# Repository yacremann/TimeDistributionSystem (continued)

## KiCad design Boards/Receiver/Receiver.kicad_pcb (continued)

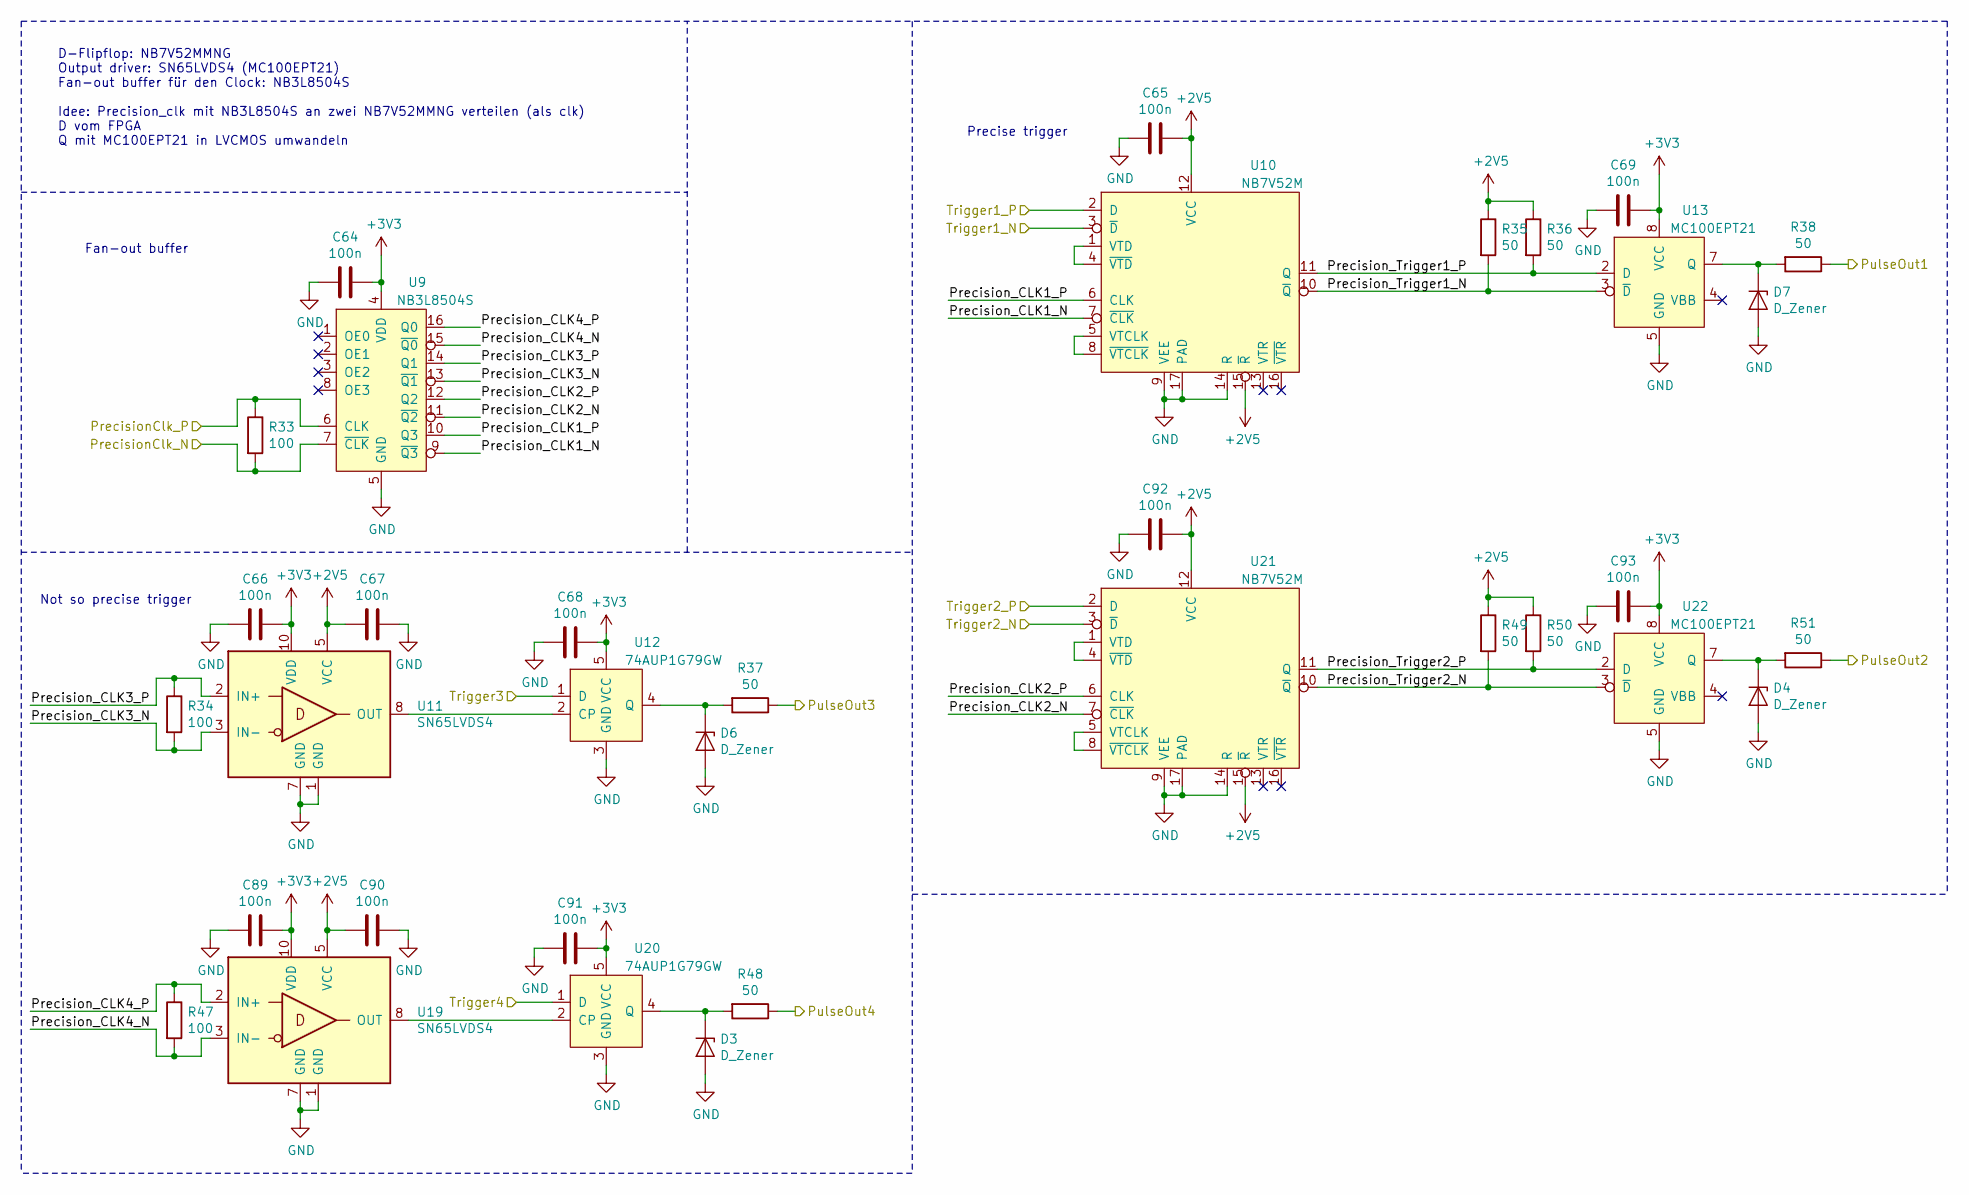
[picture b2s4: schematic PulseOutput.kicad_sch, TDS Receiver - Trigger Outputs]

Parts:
C64, C65, C66, C67, C68, C69, C89, C90, C91, C92, C93: 100n; C_0603_1608Metric
D3, D4, D6, D7: D_Zener; D_0805_2012Metric
R33, R34, R47: 100; R_0603_1608Metric
R35, R36, R37, R38, R48, R49, R50, R51: 50; R_0603_1608Metric
U9: NB3L8504S; TSSOP-16_4.4x5mm_P0.65mm
U10, U21: NB7V52M; QFN-16-1EP_3x3mm_P0.5mm_EP1.9x1.9mm
U11, U19: SN65LVDS4; Texas_R-PUQFN-N10
U12, U20: 74AUP1G79GW; SOT-353_SC-70-5_Handsoldering
U13, U22: MC100EPT21; TSSOP-8_3x3mm_P0.65mm

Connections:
+2V5: C65.1, C67.2, C90.2, C92.1, R35.1, R36.1, R49.1, R50.1, U10.12 (VCC), U10.15 (~R), U11.5 (VCC), U19.5 (VCC), U21.12 (VCC), U21.15 (~R); also elsewhere on the board
+3V3: C64.1, C66.1, C68.1, C69.1, C89.1, C91.1, C93.1, U9.4 (VDD), U11.10 (VDD), U12.5 (VCC), U13.8 (VCC), U19.10 (VDD), U20.5 (VCC), U22.8 (VCC); also elsewhere on the board
/PrecisionClk_N: R33.2, U9.7 (~CLK); also elsewhere on the board
/PrecisionClk_P: R33.1, U9.6 (CLK); also elsewhere on the board
/PulseOutput/Precision_CLK1_N: U9.9 (~Q3), U10.7 (~CLK)
/PulseOutput/Precision_CLK1_P: U9.10 (Q3), U10.6 (CLK)
/PulseOutput/Precision_CLK2_N: U9.11 (~Q2), U21.7 (~CLK)
/PulseOutput/Precision_CLK2_P: U9.12 (Q2), U21.6 (CLK)
/PulseOutput/Precision_CLK3_N: R34.2, U9.13 (~Q1), U11.3 (IN-)
/PulseOutput/Precision_CLK3_P: R34.1, U9.14 (Q1), U11.2 (IN+)
/PulseOutput/Precision_CLK4_N: R47.2, U9.15 (~Q0), U19.3 (IN-)
/PulseOutput/Precision_CLK4_P: R47.1, U9.16 (Q0), U19.2 (IN+)
/PulseOutput/Precision_Trigger1_N: R35.2, U10.10 (~Q), U13.3 (~D)
/PulseOutput/Precision_Trigger1_P: R36.2, U10.11 (Q), U13.2 (D)
/PulseOutput/Precision_Trigger2_N: R49.2, U21.10 (~Q), U22.3 (~D)
/PulseOutput/Precision_Trigger2_P: R50.2, U21.11 (Q), U22.2 (D)
/PulseOutput/PulseOut1: R38.1; also elsewhere on the board
/PulseOutput/PulseOut2: R51.1; also elsewhere on the board
/PulseOutput/PulseOut3: R37.1; also elsewhere on the board
/PulseOutput/PulseOut4: R48.1; also elsewhere on the board
/Trigger1_N: U10.3 (~D); also elsewhere on the board
/Trigger1_P: U10.2 (D); also elsewhere on the board
/Trigger2_N: U21.3 (~D); also elsewhere on the board
/Trigger2_P: U21.2 (D); also elsewhere on the board
/Trigger3: U12.1 (D); also elsewhere on the board
/Trigger4: U20.1 (D); also elsewhere on the board
GND: C64.2, C65.2, C66.2, C67.1, C68.2, C69.2, C89.2, C90.1, C91.2, C92.2, C93.2, D3.2 (A), D4.2 (A), D6.2 (A), D7.2 (A), U9.5 (GND), U10.9 (VEE), U10.14 (R), U10.17 (PAD), U11.1 (GND), U11.7 (GND), U12.3 (GND), U13.5 (GND), U19.1 (GND), U19.7 (GND), U20.3 (GND), U21.9 (VEE), U21.14 (R), U21.17 (PAD), U22.5 (GND); also elsewhere on the board
unnamed: D3.1 (K), R48.2, U20.4 (Q)
unnamed: D4.1 (K), R51.2, U22.7 (Q)
unnamed: D6.1 (K), R37.2, U12.4 (Q)
unnamed: D7.1 (K), R38.2, U13.7 (Q)
unnamed: U10.1 (VTD), U10.4 (~VTD)
unnamed: U10.5 (VTCLK), U10.8 (~VTCLK)
unnamed: U11.8 (OUT), U12.2 (CP)
unnamed: U19.8 (OUT), U20.2 (CP)
unnamed: U21.1 (VTD), U21.4 (~VTD)
unnamed: U21.5 (VTCLK), U21.8 (~VTCLK)

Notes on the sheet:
D-Flipflop: NB7V52MMNG Output driver: SN65LVDS4 (MC100EPT21) Fan-out buffer für den Clock: NB3L8504S Idee: Precision_clk mit NB3L8504S an zwei NB7V52MMNG verteilen (als clk) D vom FPGA Q mit MC100EPT21 in LVCMOS umwandeln
Precise trigger
Not so precise trigger
Fan-out buffer

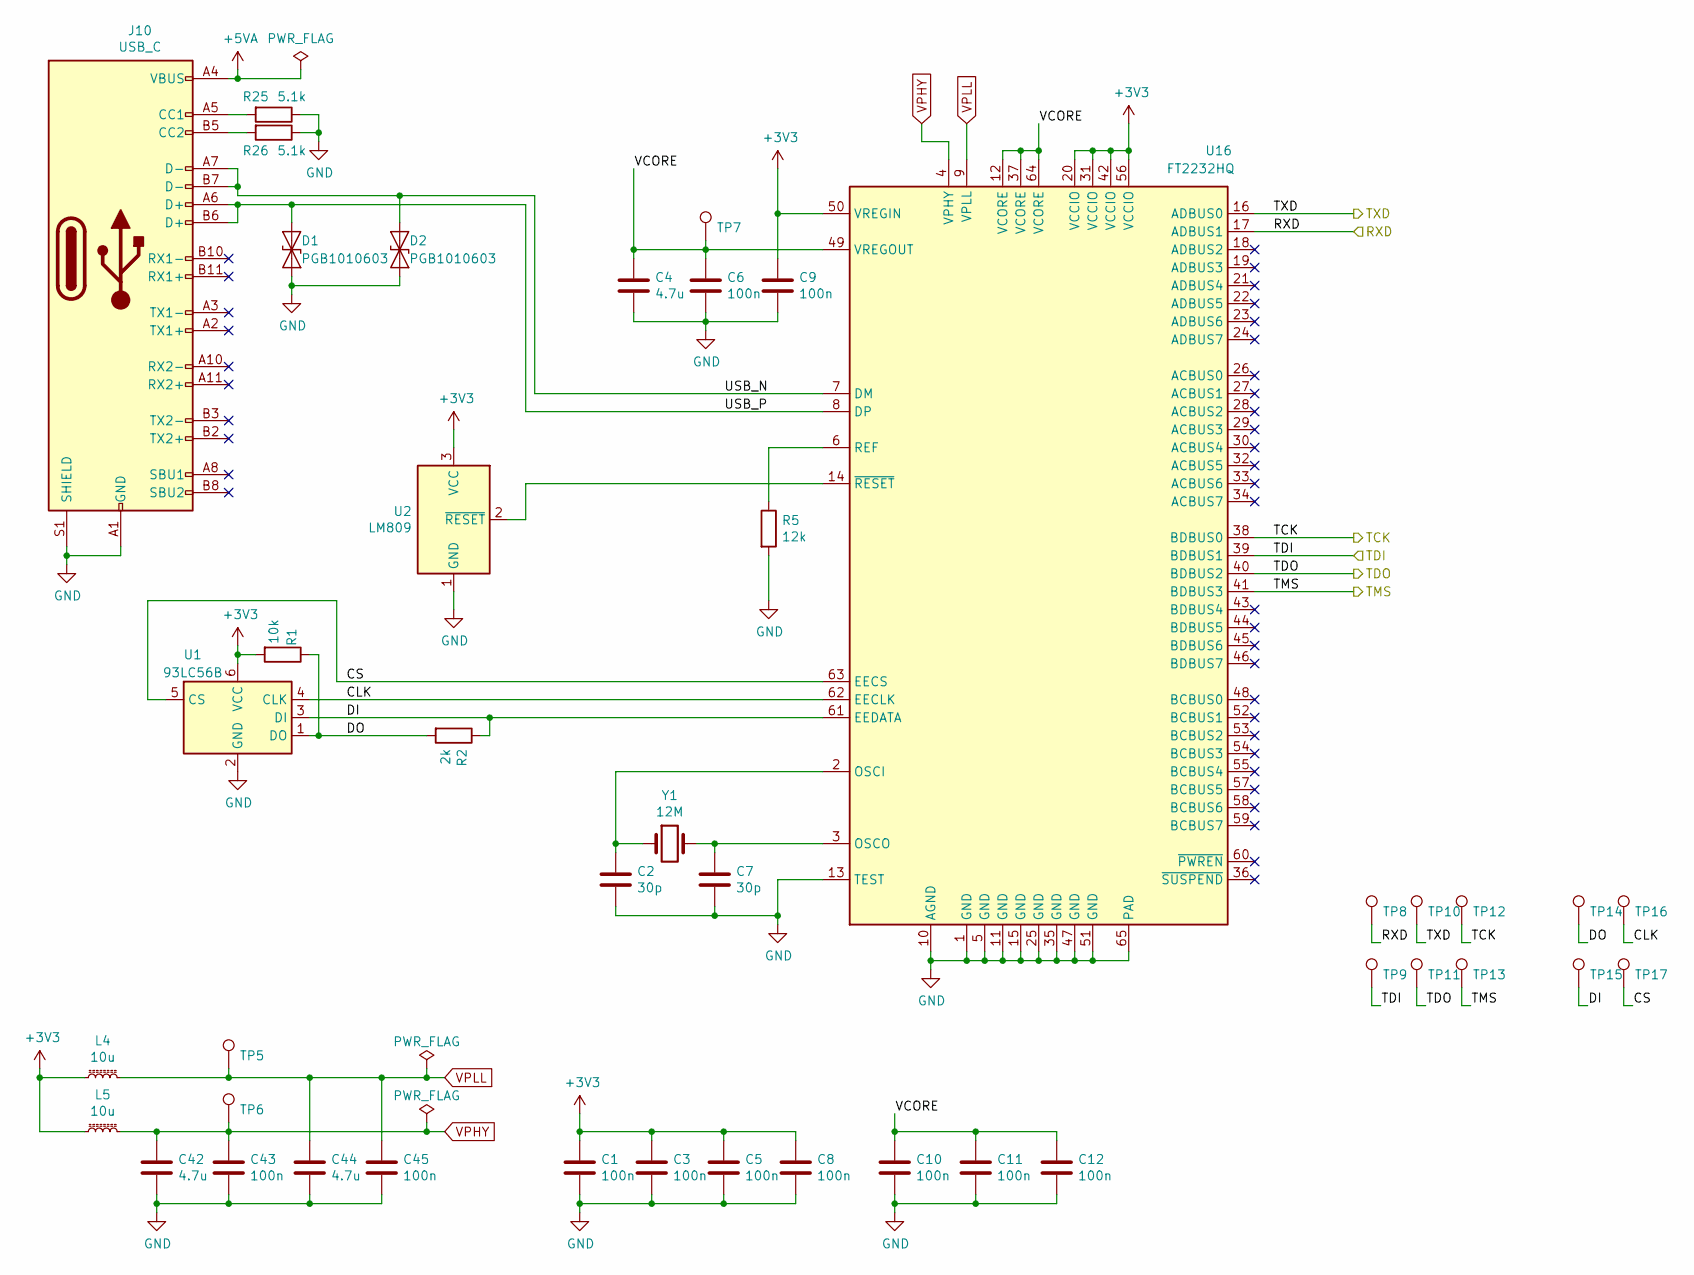
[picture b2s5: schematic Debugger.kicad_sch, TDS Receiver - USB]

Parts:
C1, C3, C5, C6, C8, C9, C10, C11, C12, C43, C45: 100n; C_0603_1608Metric
C2, C7: 30p; C_0603_1608Metric
C4, C42, C44: 4.7u; C_0603_1608Metric
D1, D2: PGB1010603; D_0603_1608Metric
J10: USB_C; USB_C_Receptacle_Amphenol_12401610E4-2A_CircularHoles
L4, L5: 10u; L_1008_2520Metric
R1: 10k; R_0603_1608Metric
R2: 2k; R_0603_1608Metric
R5: 12k; R_0603_1608Metric
R25, R26: 5.1k; R_0603_1608Metric
TP5, TP6, TP7, TP8, TP9, TP10, TP11, TP12, TP13, TP14, TP15, TP16, TP17: TestPoint; TestPoint_THTPad_D1.5mm_Drill0.7mm
U1: 93LC56B; SOT-23-6
U2: LM809; SOT-23
U16: FT2232HQ; QFN-64-1EP_9x9mm_P0.5mm_EP4.35x4.35mm
Y1: 12M; Crystal_SMD_5032-2Pin_5.0x3.2mm

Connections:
+3V3: C1.1, C3.1, C5.1, C8.1, C9.1, L4.1, L5.1, R1.2, U1.6 (VCC), U2.3 (VCC), U16.20 (VCCIO), U16.31 (VCCIO), U16.42 (VCCIO), U16.50 (VREGIN), U16.56 (VCCIO); also elsewhere on the board
+5VA: J10.A4 (VBUS), J10.A9 (VBUS), J10.B4 (VBUS), J10.B9 (VBUS); also elsewhere on the board
/CDR_PLL/RXD: TP10.1, U16.16 (ADBUS0); also elsewhere on the board
/CDR_PLL/TCK: TP12.1, U16.38 (BDBUS0); also elsewhere on the board
/CDR_PLL/TDI: TP9.1, U16.39 (BDBUS1); also elsewhere on the board
/CDR_PLL/TDO: TP11.1, U16.40 (BDBUS2); also elsewhere on the board
/CDR_PLL/TMS: TP13.1, U16.41 (BDBUS3); also elsewhere on the board
/Debugger/CLK: TP16.1, U1.4 (CLK), U16.62 (EECLK)
/Debugger/CS: TP17.1, U1.5 (CS), U16.63 (EECS)
/Debugger/DI: R2.1, TP15.1, U1.3 (DI), U16.61 (EEDATA)
/Debugger/DO: R1.1, R2.2, TP14.1, U1.1 (DO)
/Debugger/RXD: TP8.1, U16.17 (ADBUS1); also elsewhere on the board
/Debugger/USB_N: D2.1 (A1), J10.A7 (D-), J10.B7 (D-), U16.7 (DM)
/Debugger/USB_P: D1.1 (A1), J10.A6 (D+), J10.B6 (D+), U16.8 (DP)
/Debugger/VCORE: C4.1, C6.1, C10.1, C11.1, C12.1, TP7.1, U16.12 (VCORE), U16.37 (VCORE), U16.49 (VREGOUT), U16.64 (VCORE)
GND: C1.2, C2.2, C3.2, C4.2, C5.2, C6.2, C7.2, C8.2, C9.2, C10.2, C11.2, C12.2, C42.2, C43.2, C44.2, C45.2, D1.2 (A2), D2.2 (A2), J10.A1 (GND), J10.A12 (GND), J10.B1 (GND), J10.B12 (GND), J10.S1 (SHIELD), R5.2, R25.1, R26.1, U1.2 (GND), U2.1 (GND), U16.1 (GND), U16.5 (GND), U16.10 (AGND), U16.11 (GND), U16.13 (TEST), U16.15 (GND), U16.25 (GND), U16.35 (GND), U16.47 (GND), U16.51 (GND), U16.65 (PAD); also elsewhere on the board
unnamed: C2.1, U16.2 (OSCI), Y1.1
unnamed: C7.1, U16.3 (OSCO), Y1.2
unnamed: J10.A5 (CC1), R25.2
unnamed: J10.B5 (CC2), R26.2
unnamed: R5.1, U16.6 (REF)
unnamed: U2.2 (~RESET), U16.14 (~RESET)
VPHY: C42.1, C43.1, L5.2, TP6.1, U16.4 (VPHY)
VPLL: C44.1, C45.1, L4.2, TP5.1, U16.9 (VPLL)

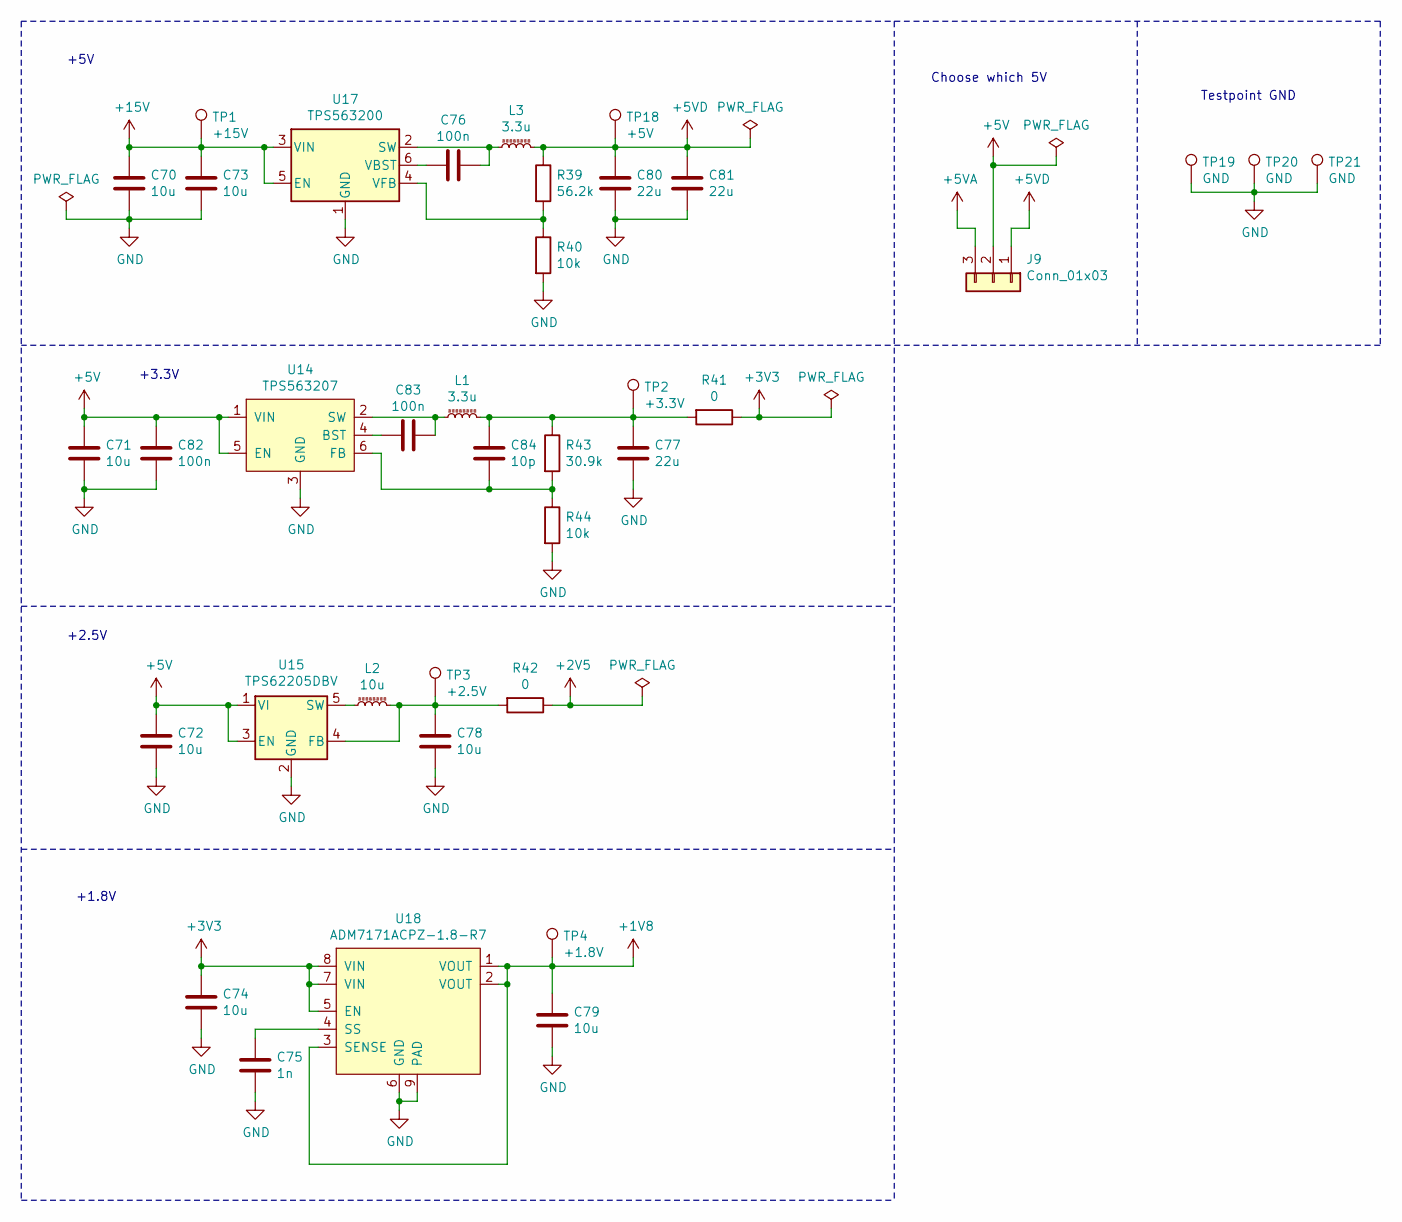
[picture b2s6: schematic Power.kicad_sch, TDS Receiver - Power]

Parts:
C70, C71, C72, C73, C74, C78, C79: 10u; C_0603_1608Metric
C75: 1n; C_0603_1608Metric
C76, C82, C83: 100n; C_0603_1608Metric
C77, C80, C81: 22u; C_0603_1608Metric
C84: 10p; C_0603_1608Metric
J9: Conn_01x03; PinHeader_1x03_P2.54mm_Vertical
L1, L3: 3.3u; L_Bourns-SRN8040_8x8.15mm
L2: 10u; L_1008_2520Metric
R39: 56.2k; R_0603_1608Metric
R40, R44: 10k; R_0603_1608Metric
R41: 0; R_1206_3216Metric
R42: 0; R_0603_1608Metric
R43: 30.9k; R_0603_1608Metric
TP1: +15V; TestPoint_THTPad_D1.5mm_Drill0.7mm
TP2: +3.3V; TestPoint_THTPad_D1.5mm_Drill0.7mm
TP3: +2.5V; TestPoint_THTPad_D1.5mm_Drill0.7mm
TP4: +1.8V; TestPoint_THTPad_D1.5mm_Drill0.7mm
TP18: +5V; TestPoint_THTPad_D1.5mm_Drill0.7mm
TP19, TP20, TP21: GND; TestPoint_THTPad_D1.5mm_Drill0.7mm
U14: TPS563207; SOT-563
U15: TPS62205DBV; SOT-23-5
U17: TPS563200; SOT-23-6
U18: ADM7171ACPZ-1.8-R7; LFCSP-8-1EP_3x3mm_P0.5mm_EP1.45x1.74mm

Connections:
+1V8: C79.1, TP4.1, U18.1 (VOUT), U18.2 (VOUT), U18.3 (SENSE); also elsewhere on the board
+2V5: R42.1; also elsewhere on the board
+3V3: C74.1, R41.1, U18.5 (EN), U18.7 (VIN), U18.8 (VIN); also elsewhere on the board
+5V: C71.1, C72.1, C82.1, J9.2, U14.1 (VIN), U14.5 (EN), U15.1 (VI), U15.3 (EN)
+5VA: J9.3; also elsewhere on the board
+5VD: C80.1, C81.1, J9.1, L3.2, R39.1, TP18.1
+15V: C70.1, C73.1, TP1.1, U17.3 (VIN), U17.5 (EN); also elsewhere on the board
GND: C70.2, C71.2, C72.2, C73.2, C74.2, C75.2, C77.2, C78.2, C79.2, C80.2, C81.2, C82.2, R40.2, R44.2, TP19.1, TP20.1, TP21.1, U14.3 (GND), U15.2 (GND), U17.1 (GND), U18.6 (GND), U18.9 (PAD); also elsewhere on the board
unnamed: C75.1, U18.4 (SS)
unnamed: C76.1, L3.1, U17.2 (SW)
unnamed: C76.2, U17.6 (VBST)
unnamed: C77.1, C84.1, L1.2, R41.2, R43.1, TP2.1
unnamed: C78.1, L2.2, R42.2, TP3.1, U15.4 (FB)
unnamed: C83.1, L1.1, U14.2 (SW)
unnamed: C83.2, U14.4 (BST)
unnamed: C84.2, R43.2, R44.1, U14.6 (FB)
unnamed: L2.1, U15.5 (SW)
unnamed: R39.2, R40.1, U17.4 (VFB)

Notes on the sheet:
Testpoint GND
+3.3V
Choose which 5V
+5V
+2.5V
+1.8V

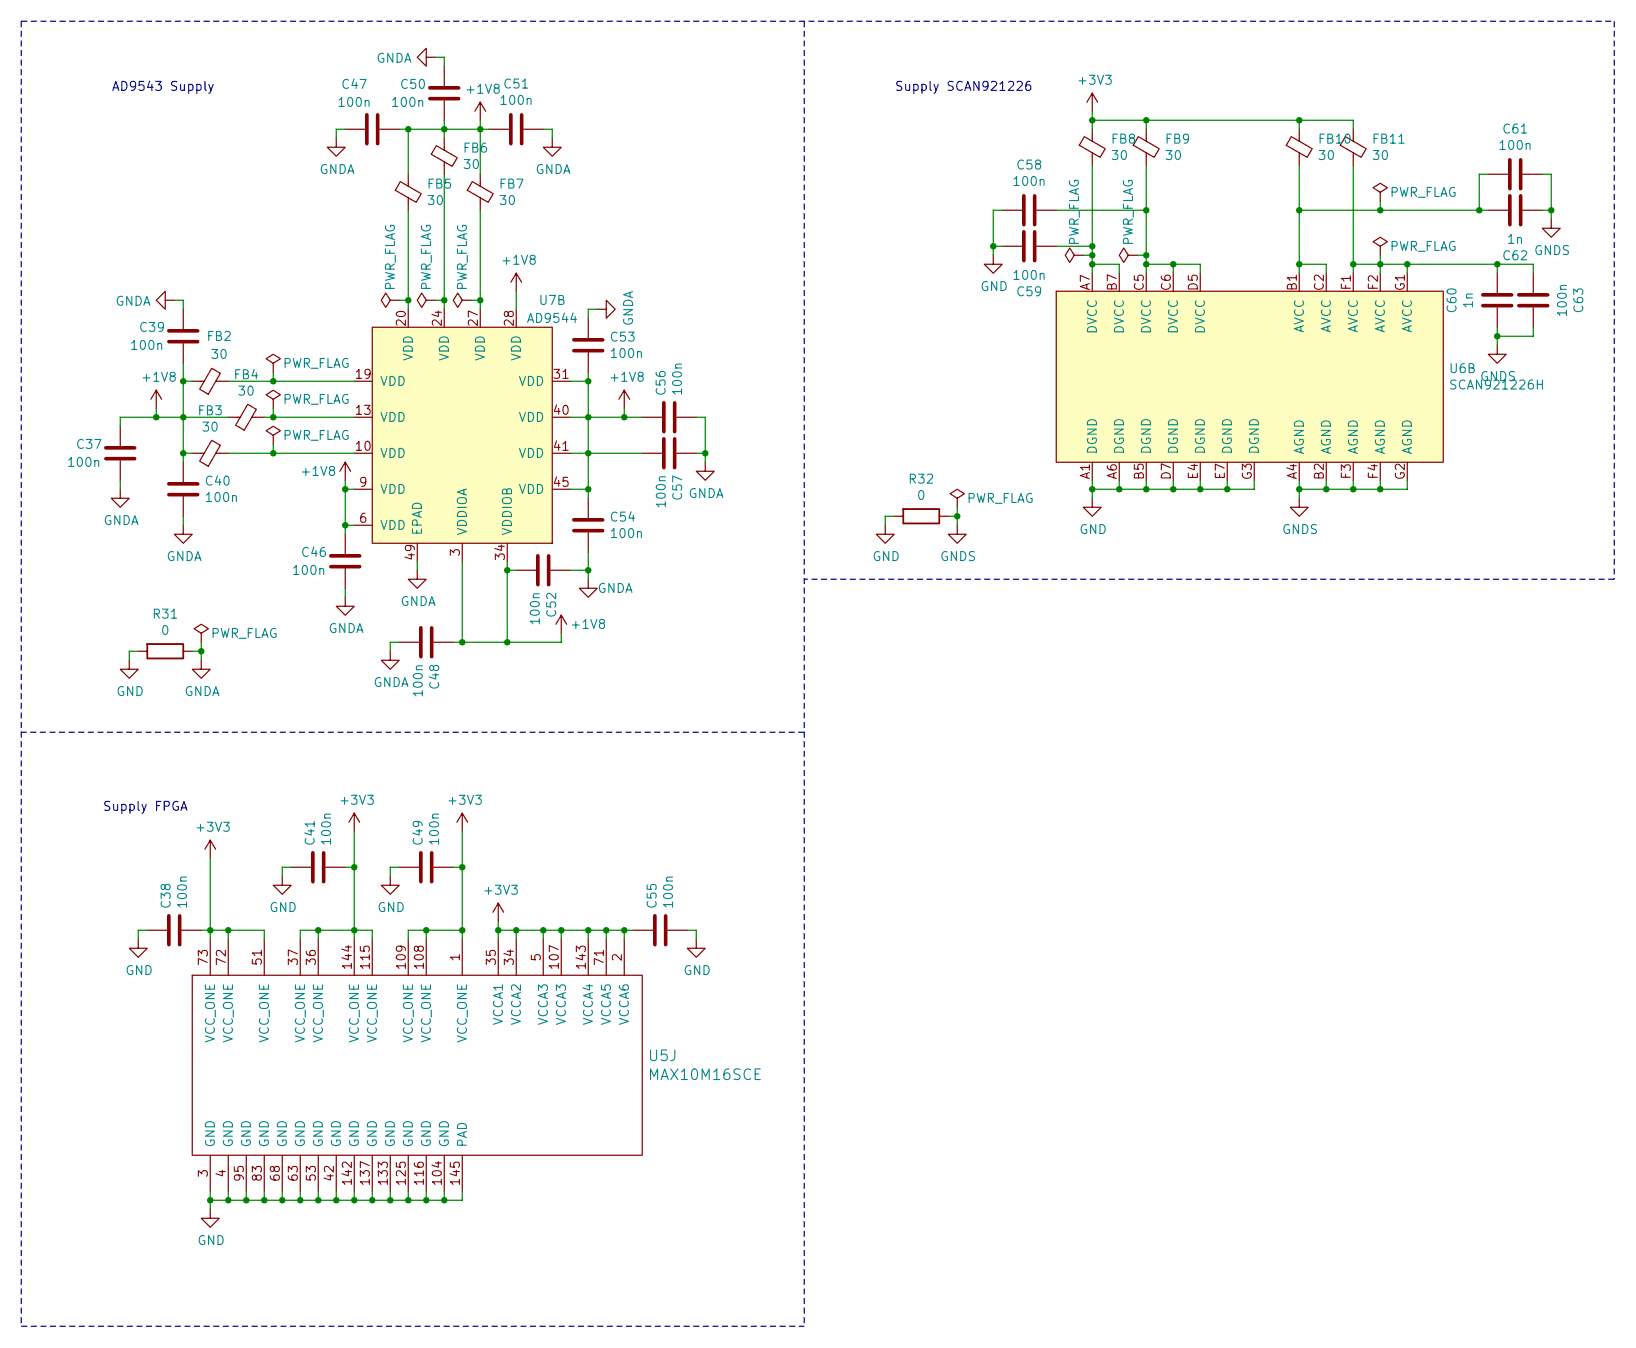
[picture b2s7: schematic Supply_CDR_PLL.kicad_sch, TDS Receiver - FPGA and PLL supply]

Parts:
C37, C39, C40, C47, C48, C50, C51, C52, C53, C54, C56, C57: 100n; C_0402_1005Metric
C38, C41, C46, C49, C55, C58, C59, C61, C63: 100n; C_0603_1608Metric
C60, C62: 1n; C_0603_1608Metric
FB2, FB3, FB4, FB5, FB6, FB7, FB8, FB9, FB10, FB11: 30; L_0402_1005Metric
R31, R32: 0; R_0603_1608Metric
U5: MAX10M16SCE; EQFP_144
U6: SCAN921226H; BGA-49_7x7_7.0x7.0mm
U7: AD9544; LFCSP-48-1EP_7x7mm_P0.5mm_EP4.1x4.1mm

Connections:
+1V8: C37.1, C39.2, C40.1, C46.1, C47.1, C48.1, C50.2, C51.2, C52.2, C53.2, C54.1, C56.1, C57.2, FB2.1, FB3.1, FB4.1, FB5.1, FB6.1, FB7.1, U7.3 (VDDIOA), U7.6 (VDD), U7.9 (VDD), U7.28 (VDD), U7.31 (VDD), U7.34 (VDDIOB), U7.40 (VDD), U7.41 (VDD), U7.45 (VDD); also elsewhere on the board
+3V3: C38.2, C41.2, C49.2, C55.1, FB8.1, FB9.1, FB10.1, FB11.1, U5.1 (VCC_ONE), U5.2 (VCCA6), U5.5 (VCCA3), U5.34 (VCCA2), U5.35 (VCCA1), U5.36 (VCC_ONE), U5.37 (VCC_ONE), U5.51 (VCC_ONE), U5.71 (VCCA5), U5.72 (VCC_ONE), U5.73 (VCC_ONE), U5.107 (VCCA3), U5.108 (VCC_ONE), U5.109 (VCC_ONE), U5.115 (VCC_ONE), U5.143 (VCCA4), U5.144 (VCC_ONE); also elsewhere on the board
GND: C38.1, C41.1, C49.1, C55.2, C58.2, C59.1, R31.2, R32.2, U5.3 (GND), U5.4 (GND), U5.42 (GND), U5.53 (GND), U5.63 (GND), U5.68 (GND), U5.83 (GND), U5.95 (GND), U5.104 (GND), U5.116 (GND), U5.125 (GND), U5.133 (GND), U5.137 (GND), U5.142 (GND), U5.145 (PAD), U6.A1 (DGND), U6.A6 (DGND), U6.B5 (DGND), U6.D7 (DGND), U6.E4 (DGND), U6.E7 (DGND), U6.G3 (DGND); also elsewhere on the board
GNDA: C37.2, C39.1, C40.2, C46.2, C47.2, C48.2, C50.1, C51.1, C52.1, C53.1, C54.2, C56.2, C57.1, R31.1, U7.49 (EPAD); also elsewhere on the board
GNDS: C60.2, C61.1, C62.2, C63.1, R32.1, U6.A4 (AGND), U6.B2 (AGND), U6.F3 (AGND), U6.F4 (AGND), U6.G2 (AGND)
unnamed: C58.1, FB9.2, U6.C5 (DVCC), U6.C6 (DVCC), U6.D5 (DVCC)
unnamed: C59.2, FB8.2, U6.A7 (DVCC), U6.B7 (DVCC)
unnamed: C60.1, C63.2, FB11.2, U6.F1 (AVCC), U6.F2 (AVCC), U6.G1 (AVCC)
unnamed: C61.2, C62.1, FB10.2, U6.B1 (AVCC), U6.C2 (AVCC)
unnamed: FB2.2, U7.19 (VDD)
unnamed: FB3.2, U7.10 (VDD)
unnamed: FB4.2, U7.13 (VDD)
unnamed: FB5.2, U7.20 (VDD)
unnamed: FB6.2, U7.24 (VDD)
unnamed: FB7.2, U7.27 (VDD)

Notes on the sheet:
Supply SCAN921226
Supply FPGA
AD9543 Supply

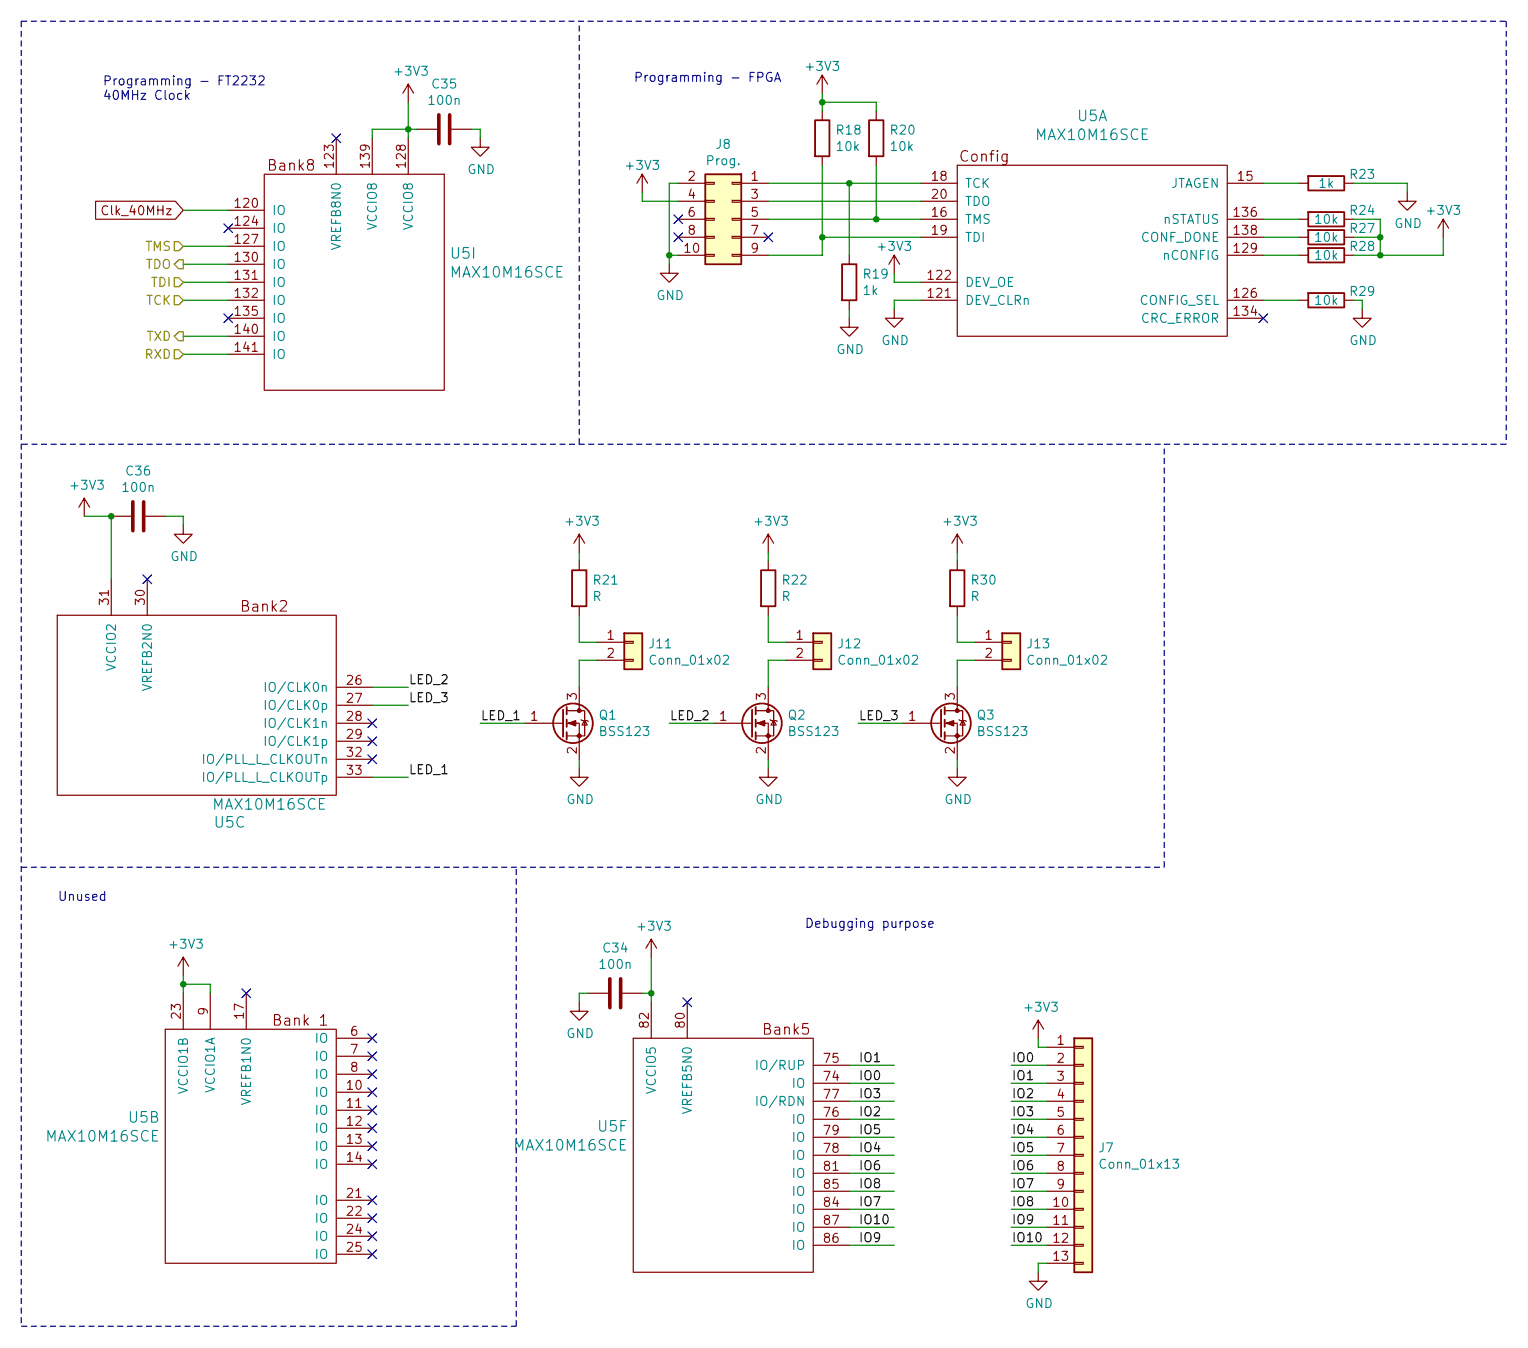
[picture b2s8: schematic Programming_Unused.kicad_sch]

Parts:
C34, C35, C36: 100n; C_0603_1608Metric
J7: Conn_01x13; PinHeader_1x13_P2.54mm_Vertical
J8: Prog.; IDC-Header_2x05_P2.54mm_Vertical
J11, J12, J13: Conn_01x02; TerminalBlock_Phoenix_MKDS-1,5-2-5.08_1x02_P5.08mm_Horizont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
Q1, Q2, Q3: BSS123; SOT-23
R18, R20, R24, R27, R28, R29: 10k; R_0603_1608Metric
R19, R23: 1k; R_0603_1608Metric
R21, R22, R30: R; R_0603_1608Metric
U5: MAX10M16SCE; EQFP_144

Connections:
+3V3: C34.1, C35.2, C36.2, J7.1, J8.4, R18.1, R20.1, R21.1, R22.1, R24.1, R27.1, R28.1, R30.1, U5.9 (VCCIO1A), U5.23 (VCCIO1B), U5.31 (VCCIO2), U5.82 (VCCIO5), U5.122 (DEV_OE), U5.128 (VCCIO8), U5.139 (VCCIO8); also elsewhere on the board
/CDR_PLL/Programming_Unused/IO0: J7.2, U5.74 (IO)
/CDR_PLL/Programming_Unused/IO1: J7.3, U5.75 (IO/RUP)
/CDR_PLL/Programming_Unused/IO2: J7.4, U5.76 (IO)
/CDR_PLL/Programming_Unused/IO3: J7.5, U5.77 (IO/RDN)
/CDR_PLL/Programming_Unused/IO4: J7.6, U5.78 (IO)
/CDR_PLL/Programming_Unused/IO5: J7.7, U5.79 (IO)
/CDR_PLL/Programming_Unused/IO6: J7.8, U5.81 (IO)
/CDR_PLL/Programming_Unused/IO7: J7.9, U5.84 (IO)
/CDR_PLL/Programming_Unused/IO8: J7.10, U5.85 (IO)
/CDR_PLL/Programming_Unused/IO9: J7.11, U5.86 (IO)
/CDR_PLL/Programming_Unused/IO10: J7.12, U5.87 (IO)
/CDR_PLL/Programming_Unused/LED_1: Q1.1 (G), U5.33 (IO/PLL_L_CLKOUTp)
/CDR_PLL/Programming_Unused/LED_2: Q2.1 (G), U5.26 (IO/CLK0n)
/CDR_PLL/Programming_Unused/LED_3: Q3.1 (G), U5.27 (IO/CLK0p)
/CDR_PLL/RXD: U5.141 (IO); also elsewhere on the board
/CDR_PLL/TCK: U5.132 (IO); also elsewhere on the board
/CDR_PLL/TDI: U5.130 (IO); also elsewhere on the board
/CDR_PLL/TDO: U5.131 (IO); also elsewhere on the board
/CDR_PLL/TMS: U5.127 (IO); also elsewhere on the board
/Debugger/RXD: U5.140 (IO); also elsewhere on the board
Clk_40MHz: U5.120 (IO); also elsewhere on the board
GND: C34.2, C35.1, C36.1, J7.13, J8.2, J8.10, Q1.2 (S), Q2.2 (S), Q3.2 (S), R19.2, R23.1, R29.1, U5.121 (DEV_CLRn); also elsewhere on the board
unnamed: J8.1, R19.1, U5.18 (TCK)
unnamed: J8.3, U5.20 (TDO)
unnamed: J8.5, R20.2, U5.16 (TMS)
unnamed: J8.9, R18.2, U5.19 (TDI)
unnamed: J11.1, R21.2
unnamed: J11.2, Q1.3 (D)
unnamed: J12.1, R22.2
unnamed: J12.2, Q2.3 (D)
unnamed: J13.1, R30.2
unnamed: J13.2, Q3.3 (D)
unnamed: R23.2, U5.15 (JTAGEN)
unnamed: R24.2, U5.136 (nSTATUS)
unnamed: R27.2, U5.138 (CONF_DONE)
unnamed: R28.2, U5.129 (nCONFIG)
unnamed: R29.2, U5.126 (CONFIG_SEL)

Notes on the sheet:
Programming - FPGA
Unused
Debugging purpose
Programming - FT2232 40MHz Clock

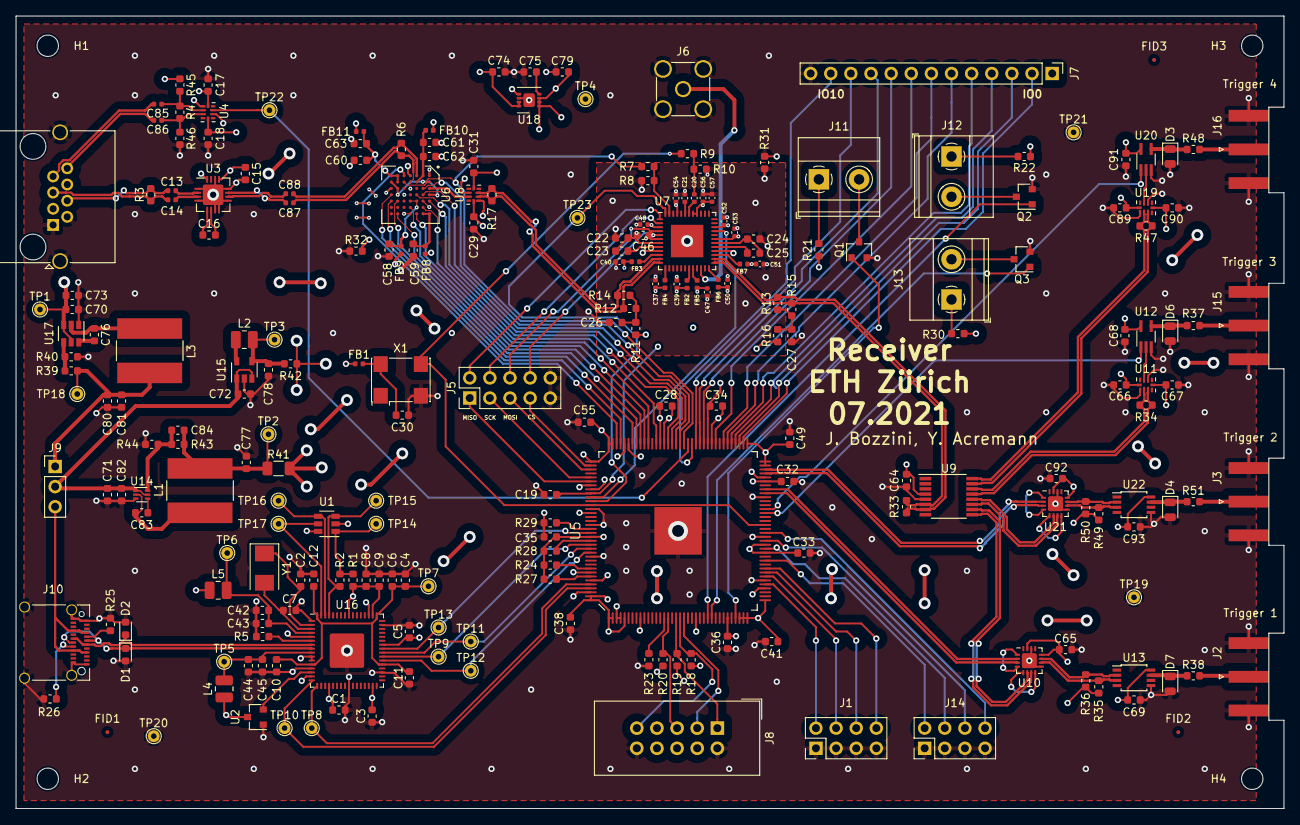
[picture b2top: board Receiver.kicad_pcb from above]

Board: 4 copper layers, 160.0 x 100.0 mm, 239 parts (0 on the bottom side), 176 nets.

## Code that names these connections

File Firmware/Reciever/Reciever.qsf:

# -------------------------------------------------------------------------- #
#
# Copyright (C) 2020  Intel Corporation. All rights reserved.
# Your use of Intel Corporation's design tools, logic functions 
# and other software and tools, and any partner logic 
# functions, and any output files from any of the foregoing 
# (including device programming or simulation files), and any 
# associated documentation or information are expressly subject 
# to the terms and conditions of the Intel Program License 
# Subscription Agreement, the Intel Quartus Prime License Agreement,
# the Intel FPGA IP License Agreement, or other applicable license
# agreement, including, without limitation, that your use is for
# the sole purpose of programming logic devices manufactured by
# Intel and sold by Intel or its authorized distributors.  Please
# refer to the applicable agreement for further details, at
# https://fpgasoftware.intel.com/eula.
#
# -------------------------------------------------------------------------- #
#
# Quartus Prime
# Version 20.1.0 Build 711 06/05/2020 SJ Lite Edition
# Date created = 17:26:31  Juli 08, 2021
#
# -------------------------------------------------------------------------- #
#
# Notes:
#
# 1) The default values for assignments are stored in the file:
#		Reciever_assignment_defaults.qdf
#    If this file doesn't exist, see file:
#		assignment_defaults.qdf
#
# 2) Altera recommends that you do not modify this file. This
#    file is updated automatically by the Quartus Prime software
#    and any changes you make may be lost or overwritten.
#
# -------------------------------------------------------------------------- #


set_global_assignment -name FAMILY "MAX 10"
set_global_assignment -name DEVICE 10M16SCE144A7G
set_global_assignment -name TOP_LEVEL_ENTITY Reciever
set_global_assignment -name ORIGINAL_QUARTUS_VERSION 20.1.0
set_global_assignment -name PROJECT_CREATION_TIME_DATE "17:26:31  JULI 08, 2021"
set_global_assignment -name LAST_QUARTUS_VERSION "23.1std.0 Lite Edition"
set_global_assignment -name PROJECT_OUTPUT_DIRECTORY output_files
set_global_assignment -name MIN_CORE_JUNCTION_TEMP "-40"
set_global_assignment -name MAX_CORE_JUNCTION_TEMP 125
set_global_assignment -name DEVICE_FILTER_PACKAGE EQFP
set_global_assignment -name DEVICE_FILTER_PIN_COUNT 144
set_global_assignment -name ERROR_CHECK_FREQUENCY_DIVISOR 256
set_global_assignment -name PARTITION_NETLIST_TYPE SOURCE -section_id Top
set_global_assignment -name PARTITION_FITTER_PRESERVATION_LEVEL PLACEMENT_AND_ROUTING -section_id Top
set_global_assignment -name PARTITION_COLOR 16764057 -section_id Top
set_location_assignment PIN_119 -to RESETn
set_instance_assignment -name IO_STANDARD "1.8 V" -to RESETn
set_location_assignment PIN_120 -to clk_40Mhz
set_location_assignment PIN_87 -to GPIO[10]
set_location_assignment PIN_86 -to GPIO[9]
set_location_assignment PIN_85 -to GPIO[8]
set_location_assignment PIN_84 -to GPIO[7]
set_location_assignment PIN_81 -to GPIO[6]
set_location_assignment PIN_79 -to GPIO[5]
set_location_assignment PIN_78 -to GPIO[4]
set_location_assignment PIN_77 -to GPIO[3]
set_location_assignment PIN_76 -to GPIO[2]
set_location_assignment PIN_75 -to GPIO[1]
set_location_assignment PIN_74 -to GPIO[0]
set_location_assignment PIN_106 -to LOCKn
set_location_assignment PIN_90 -to RCLKRf
set_location_assignment PIN_92 -to deserialized[0]
set_location_assignment PIN_93 -to deserialized[1]
set_location_assignment PIN_91 -to deserialized[2]
set_location_assignment PIN_96 -to deserialized[3]
set_location_assignment PIN_98 -to deserialized[4]
set_location_assignment PIN_99 -to deserialized[5]
set_location_assignment PIN_100 -to deserialized[6]
set_location_assignment PIN_102 -to deserialized[7]
set_location_assignment PIN_101 -to deserialized[8]
set_location_assignment PIN_105 -to deserialized[9]
set_location_assignment PIN_89 -to word_clk
set_location_assignment PIN_56 -to clk_40Mhz_2

set_global_assignment -name POWER_PRESET_COOLING_SOLUTION "23 MM HEAT SINK WITH 200 LFPM AIRFLOW"
set_global_assignment -name POWER_BOARD_THERMAL_MODEL "NONE (CONSERVATIVE)"
set_global_assignment -name FLOW_ENABLE_POWER_ANALYZER ON
set_global_assignment -name POWER_DEFAULT_INPUT_IO_TOGGLE_RATE "12.5 %"
set_location_assignment PIN_88 -to slow_data
set_location_assignment PIN_65 -to trigger1
set_location_assignment PIN_59 -to trigger3
set_location_assignment PIN_141 -to RX
set_location_assignment PIN_140 -to TX
set_location_assignment PIN_110 -to SPI_Timer_CSB
set_location_assignment PIN_113 -to SPI_Timer_SCLK
set_location_assignment PIN_111 -to SPI_Timer_SDI
set_location_assignment PIN_114 -to SPI_Timer_SDO
set_instance_assignment -name IO_STANDARD "1.8 V" -to SPI_Timer_CSB
set_instance_assignment -name IO_STANDARD "1.8 V" -to SPI_Timer_SCLK
set_instance_assignment -name IO_STANDARD "1.8 V" -to SPI_Timer_SDI
set_instance_assignment -name IO_STANDARD "1.8 V" -to SPI_Timer_SDO
set_location_assignment PIN_60 -to trigger4
set_instance_assignment -name IO_STANDARD LVDS -to trigger1
set_location_assignment PIN_64 -to "trigger1(n)"
set_location_assignment PIN_70 -to trigger2
set_instance_assignment -name IO_STANDARD LVDS -to trigger2
set_location_assignment PIN_69 -to "trigger2(n)"
set_location_assignment PIN_118 -to pll_locked
set_location_assignment PIN_33 -to led1
set_location_assignment PIN_26 -to led2
set_location_assignment PIN_27 -to led3
set_instance_assignment -name IO_STANDARD "1.8 V" -to pll_locked
set_location_assignment PIN_43 -to serial_o1
set_location_assignment PIN_50 -to serial_o2
set_location_assignment PIN_41 -to serial_o3
set_location_assignment PIN_47 -to serial_o4
set_global_assignment -name SYSTEMVERILOG_FILE ../general/watchdog/Watchdog.sv
set_global_assignment -name SYSTEMVERILOG_FILE ../general/SlowLink/Transmitter2/SlowTransmitter2.sv
set_global_assignment -name SYSTEMVERILOG_FILE ../general/PayloadTransmitter/PayloadTransmitter.sv
set_global_assignment -name SYSTEMVERILOG_FILE ../general/Trigger/LongDivision.sv
set_global_assignment -name SYSTEMVERILOG_FILE ../general/Trigger/Delay.sv
set_global_assignment -name SYSTEMVERILOG_FILE pulse_extender.sv
set_global_assignment -name SYSTEMVERILOG_FILE ../general/Trigger/Trigger.sv
set_global_assignment -name SYSTEMVERILOG_FILE crc_calc.sv
set_global_assignment -name SYSTEMVERILOG_FILE FrameReceiver.sv
set_global_assignment -name SYSTEMVERILOG_FILE ../general/protocol/data_frames.sv
set_global_assignment -name SYSTEMVERILOG_FILE fifo_v3.sv
set_global_assignment -name VERILOG_FILE Encode_8b10b.v
set_global_assignment -name SYSTEMVERILOG_FILE APB/ApbBus.sv
set_global_assignment -name QIP_FILE ROM/synthesis/ROM.qip
set_global_assignment -name VERILOG_FILE ROM/synthesis/ROM.v -library ROM
set_global_assignment -name VERILOG_FILE Softcore/VexRISCVSoftcore.v
set_global_assignment -name SDC_FILE Timing.sdc
set_global_assignment -name VERILOG_FILE Decode_8b10b.v
set_global_assignment -name SYSTEMVERILOG_FILE Reciever.sv
set_instance_assignment -name PARTITION_HIERARCHY root_partition -to | -section_id Top

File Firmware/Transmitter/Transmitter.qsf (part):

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set_location_assignment PIN_85 -to M0
set_location_assignment PIN_81 -to M1
set_location_assignment PIN_78 -to M2
set_location_assignment PIN_77 -to SPI_Timer_CSB
set_location_assignment PIN_75 -to SPI_Timer_SCLK
set_location_assignment PIN_76 -to SPI_Timer_SDI
set_location_assignment PIN_74 -to SPI_Timer_SDO
set_instance_assignment -name IO_STANDARD "1.8 V" -to M0
set_instance_assignment -name IO_STANDARD "1.8 V" -to M1
set_instance_assignment -name IO_STANDARD "1.8 V" -to M2
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set_location_assignment PIN_27 -to clk_80_Mhz
set_instance_assignment -name IO_STANDARD LVDS -to clk_80_Mhz
set_location_assignment PIN_26 -to "clk_80_Mhz(n)"
set_location_assignment PIN_90 -to tclkr
set_location_assignment PIN_91 -to to_serializer[9]
set_location_assignment PIN_92 -to to_serializer[8]
set_location_assignment PIN_96 -to to_serializer[7]
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set_location_assignment PIN_101 -to to_serializer[2]
set_location_assignment PIN_102 -to to_serializer[1]
set_location_assignment PIN_105 -to to_serializer[0]
set_location_assignment PIN_60 -to slow_pulse_id
set_location_assignment PIN_38 -to RX
set_location_assignment PIN_39 -to TX
set_location_assignment PIN_50 -to led1
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
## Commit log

2025-03-10 initial commit on Github
2025-03-11 fixed comments
